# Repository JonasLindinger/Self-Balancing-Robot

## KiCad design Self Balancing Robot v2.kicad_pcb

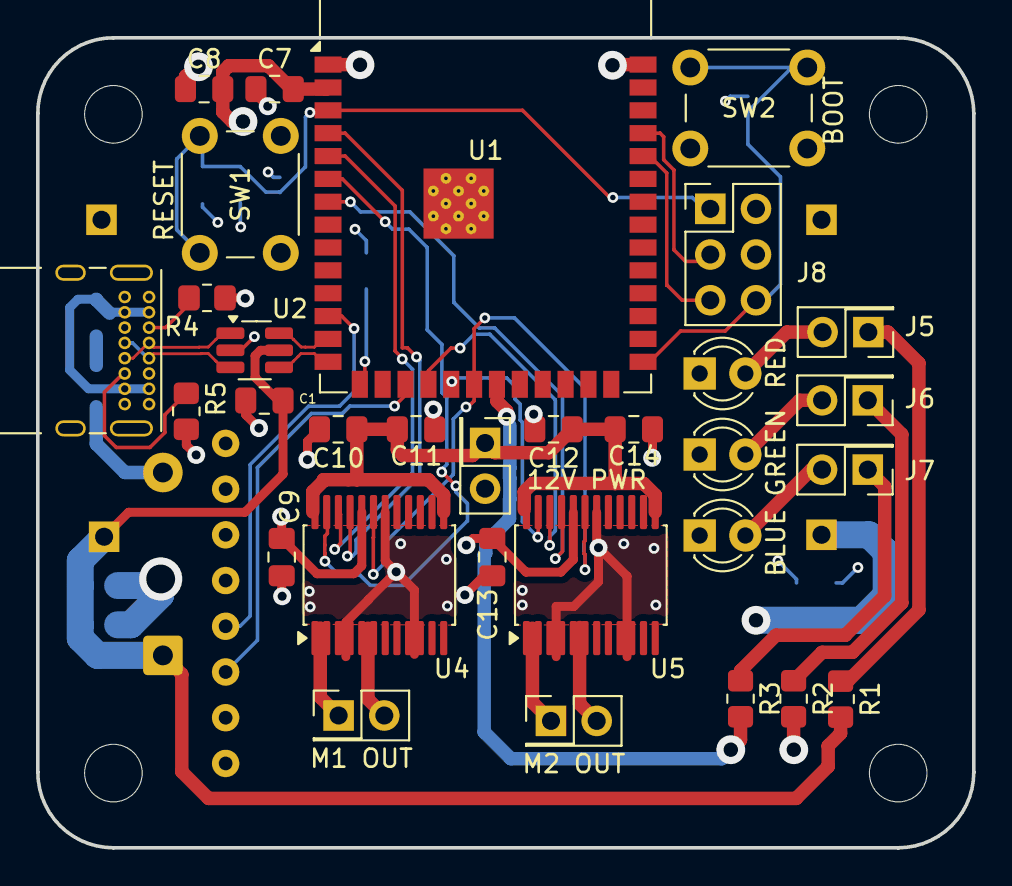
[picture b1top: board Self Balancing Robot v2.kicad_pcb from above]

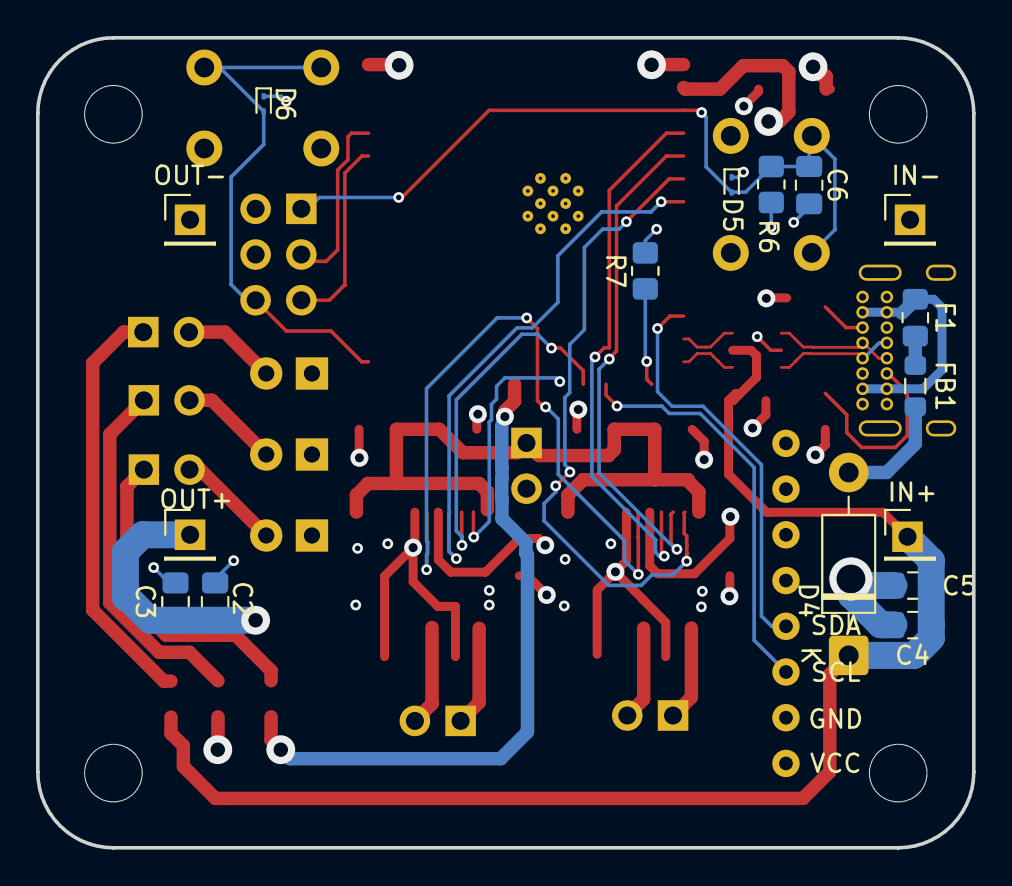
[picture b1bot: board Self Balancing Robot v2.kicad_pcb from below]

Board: 4 copper layers, 52.0 x 45.0 mm, 52 parts (17 on the bottom side), 38 nets.

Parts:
C1, C3, C5, C7, C9, C10, C13, C14: 100n; C_0805_2012Metric_Pad1.18x1.45mm_HandSolder
C2, C4, C8, C11, C12: 10u; C_0805_2012Metric_Pad1.18x1.45mm_HandSolder
C6: 1u; C_0805_2012Metric_Pad1.18x1.45mm_HandSolder
D1: RED; LED_D3.0mm
D2: GREEN; LED_D3.0mm
D3: BLUE; LED_D3.0mm
D4: 1N5817; D_DO-41_SOD81_P10.16mm_Horizontal
D5, D6: ESD9B3.3ST5G; D_SOD-923
F1: 1A; Fuse_0805_2012Metric_Pad1.15x1.40mm_HandSolder
FB1: BLM21PG220; L_0805_2012Metric_Pad1.05x1.20mm_HandSolder
H1, H2, H3, H4: MountingHole; MountingHole_3.2mm_M3_DIN965
J1: IN-; PinHeader_1x01_P2.54mm_Vertical
J2: IN+; PinHeader_1x01_P2.54mm_Vertical
J3: OUT+; PinHeader_1x01_P2.54mm_Vertical
J4: OUT-; PinHeader_1x01_P2.54mm_Vertical
J5, J6, J7: Conn_01x02; PinHeader_2x01_P2.54mm_Vertical
J8: Programming Header; PinHeader_2x03_P2.54mm_Vertical
J9: M1 OUT; PinHeader_2x01_P2.54mm_Vertical
J10: M2 OUT; PinHeader_2x01_P2.54mm_Vertical
J11: USB_C_Receptacle_USB2.0_16P; USB_C_Receptacle_GCT_USB4085
J12: 12V PWR; PinHeader_2x01_P2.54mm_Vertical
R1: 330; R_0805_2012Metric_Pad1.20x1.40mm_HandSolder
R2, R3: 100; R_0805_2012Metric_Pad1.20x1.40mm_HandSolder
R4, R5: 5.1k; R_0805_2012Metric_Pad1.20x1.40mm_HandSolder
R6, R7: 10k; R_0805_2012Metric_Pad1.20x1.40mm_HandSolder
SW1: RESET; SW_PUSH_6mm
SW2: BOOT; SW_PUSH_6mm
U1: ESP32-S3-WROOM-1
U2: USBLC6-2SC6; SOT-23-6_Handsoldering
U3: module_mpu6050
U4: M1 TB6612FNG; SSOP-24_5.3x8.2mm_P0.65mm
U5: M2 TB6612FNG; SSOP-24_5.3x8.2mm_P0.65mm

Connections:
+3V3: C2.1, C3.1, C7.2, C8.2, C9.2, C13.2, J3.1 (Pin_1_1), J8.2, R2.2, R6.2, R7.2, U1.2 (3V3), U3.1 (VCC), U4.20 (VCC), U5.20 (VCC)
+5V: C1.1, C4.1, C5.1, D4.1 (K), J2.1 (Pin_1_1), R1.2, U2.5 (VBUS)
+12V: C10.2, C11.2, C12.2, C14.2, J12.1, U4.13 (VM2), U4.14 (VM3), U4.24 (VM1), U5.13 (VM2), U5.14 (VM3), U5.24 (VM1)
/BOOT: D6.2 (A2), J8.6, SW2.2, U1.27 (IO0)
/CC1: J11.A5 (CC1), R4.1
/CC2: J11.B5 (CC2), R5.1
/CTRL LED: R3.2, U1.21 (IO13)
/D+: J11.A7 (D-), J11.B7 (D-), U2.3 (I/O2)
/D-: J11.A6 (D+), J11.B6 (D+), U2.1 (I/O1)
/EN: C6.2, D5.2 (A2), J8.1, R6.1, SW1.2, U1.3 (EN)
/IO3: R7.1, U1.15 (IO3)
/M1 IN1: U1.4 (IO4), U4.21 (AIN1)
/M1 IN2: U1.5 (IO5), U4.22 (AIN2)
/M1 OUT1: J9.1, U4.1 (AO1), U4.2 (AO1)
/M1 OUT2: J9.2, U4.5 (AO2), U4.6 (AO2)
/M1 PWM: U1.6 (IO6), U4.23 (PWMA)
/M2 IN1: U1.7 (IO7), U5.21 (AIN1)
/M2 IN2: U1.18 (IO10), U5.22 (AIN2)
/M2 OUT1: J10.1, U5.1 (AO1), U5.2 (AO1)
/M2 OUT2: J10.2, U5.5 (AO2), U5.6 (AO2)
/M2 PWM: U1.19 (IO11), U5.23 (PWMA)
/M STBY: U1.20 (IO12), U4.19 (STBY), U5.19 (STBY)
/MPU SCL: U1.17 (IO9), U3.3 (SCL)
/MPU SDA: U1.12 (IO8), U3.4 (SDA)
/RXD: J8.5, U1.36 (RXD0)
/TXD: J8.3, U1.37 (TXD0)
/USB_D+: U1.14 (USB_D+), U2.4 (I/O2)
/USB_D-: U1.13 (USB_D-), U2.6 (I/O1)
GND: C1.2, C2.2, C3.2, C4.2, C5.2, C6.1, C7.1, C8.1, C9.1, C10.1, C11.1, C12.1, C13.1, C14.1, D1.1 (K), D2.1 (K), D3.1 (K), D5.1 (A1), D6.1 (A1), J1.1 (Pin_1_1), J4.1 (Pin_1_1), J8.4, J11.A1 (GND), J11.A12 (GND), J11.B1 (GND), J11.B12 (GND), J11.SH (SHIELD), J12.2, R4.2, R5.2, SW1.1, SW2.1, U1.1 (GND), U1.40 (GND), U1.41 (GND), U2.2 (GND), U3.2 (GND), U4.3 (PGND1), U4.4 (PGND1), U4.9 (PGND2), U4.10 (PGND2), U4.18 (GND), U5.3 (PGND1), U5.4 (PGND1), U5.9 (PGND2), U5.10 (PGND2), U5.18 (GND)
unnamed: D1.2 (A), J5.2
unnamed: D2.2 (A), J6.2
unnamed: D3.2 (A), J7.2
unnamed: D4.2 (A), FB1.1
unnamed: F1.1, J11.A4 (VBUS), J11.A9 (VBUS), J11.B4 (VBUS), J11.B9 (VBUS)
unnamed: F1.2, FB1.2
unnamed: J5.1, R1.1
unnamed: J6.1, R2.1
unnamed: J7.1, R3.1

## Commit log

2026-05-23 add: hardware (kicad) and software
